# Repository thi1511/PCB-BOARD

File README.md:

# STM32WB55 RF Development Board

## 📌 Giới thiệu

Đây là thiết kế một board phát triển sử dụng vi điều khiển **STM32WB55CEU6**, được thiết kế và layout bằng **KiCad**.

Board tích hợp các khối nguồn 3.3V, USB-C, UART, SWD, BOOT/RESET, mạch dao động và khối RF Front-End với đầu nối RF coaxial.

---

## 🧩 Thành phần chính

- **MCU:** STM32WB55CEU6
- **Nguồn vào:** USB-C 5V
- **Nguồn hệ thống:** +3.3V
- **LDO:** MIC5365-3.3YD5
- **USB:** USB Type-C
- **Debug/Programming:** SWD Header
- **UART:** UART Header
- **RF Front-End:** DLF162500LT-502BA1
- **RF Connector:** Coaxial RF Connector
- **High-Speed Crystal:** 32 MHz
- **Low-Speed Crystal:** 32.768 kHz
- **BOOT:** BOOT0 Push Button
- **RESET:** NRST
- **LED:** Status LED

---

## 🔌 Các giao tiếp

### USB-C

USB-C được sử dụng để cấp nguồn và kết nối với board.

### UART

UART Header được sử dụng để giao tiếp UART với vi điều khiển.

### SWD

SWD Header hỗ trợ:

- Nạp firmware
- Debug chương trình
- Kết nối ST-LINK

### RF

Khối RF được kết nối từ STM32WB55CEU6 đến RF Front-End và đầu nối coaxial.

---

## ⚡ Khối nguồn

Nguồn **5V từ USB-C** được đưa qua IC **MIC5365-3.3YD5** để tạo nguồn **+3.3V** cho hệ thống.

Các tụ bypass và decoupling được bố trí xung quanh MCU và các khối nguồn nhằm đảm bảo nguồn hoạt động ổn định.

---

## ⏱️ Clock

Board sử dụng hai nguồn clock:

- **32 MHz crystal:** High-Speed External Clock
- **32.768 kHz crystal:** Low-Speed External Clock

---

## 🎛️ BOOT & RESET

Board được tích hợp:

- **BOOT0 Push Button:** lựa chọn chế độ boot
- **NRST:** reset MCU

---

## 📐 PCB Design

PCB được thiết kế bằng **KiCad**.

### PCB Layout

### PCB 3D View

---

## 🖥️ Schematic

Sơ đồ nguyên lý của board:

---

## 📁 Cấu trúc thư mục

```text
STM32WB55-RF-Board/
│
├── README.md
│
├── Schematic/
│   └── STM32WB55.kicad_sch
│
├── PCB/
│   ├── STM32WB55.kicad_pcb
│   └── Gerber/
│
├── Images/
│   ├── schematic.png
│   ├── pcb_layout.png
│   └── pcb_3d.png
│
├── 3D_Models/
│   └── ...
│
└── Libraries/
    └── ...

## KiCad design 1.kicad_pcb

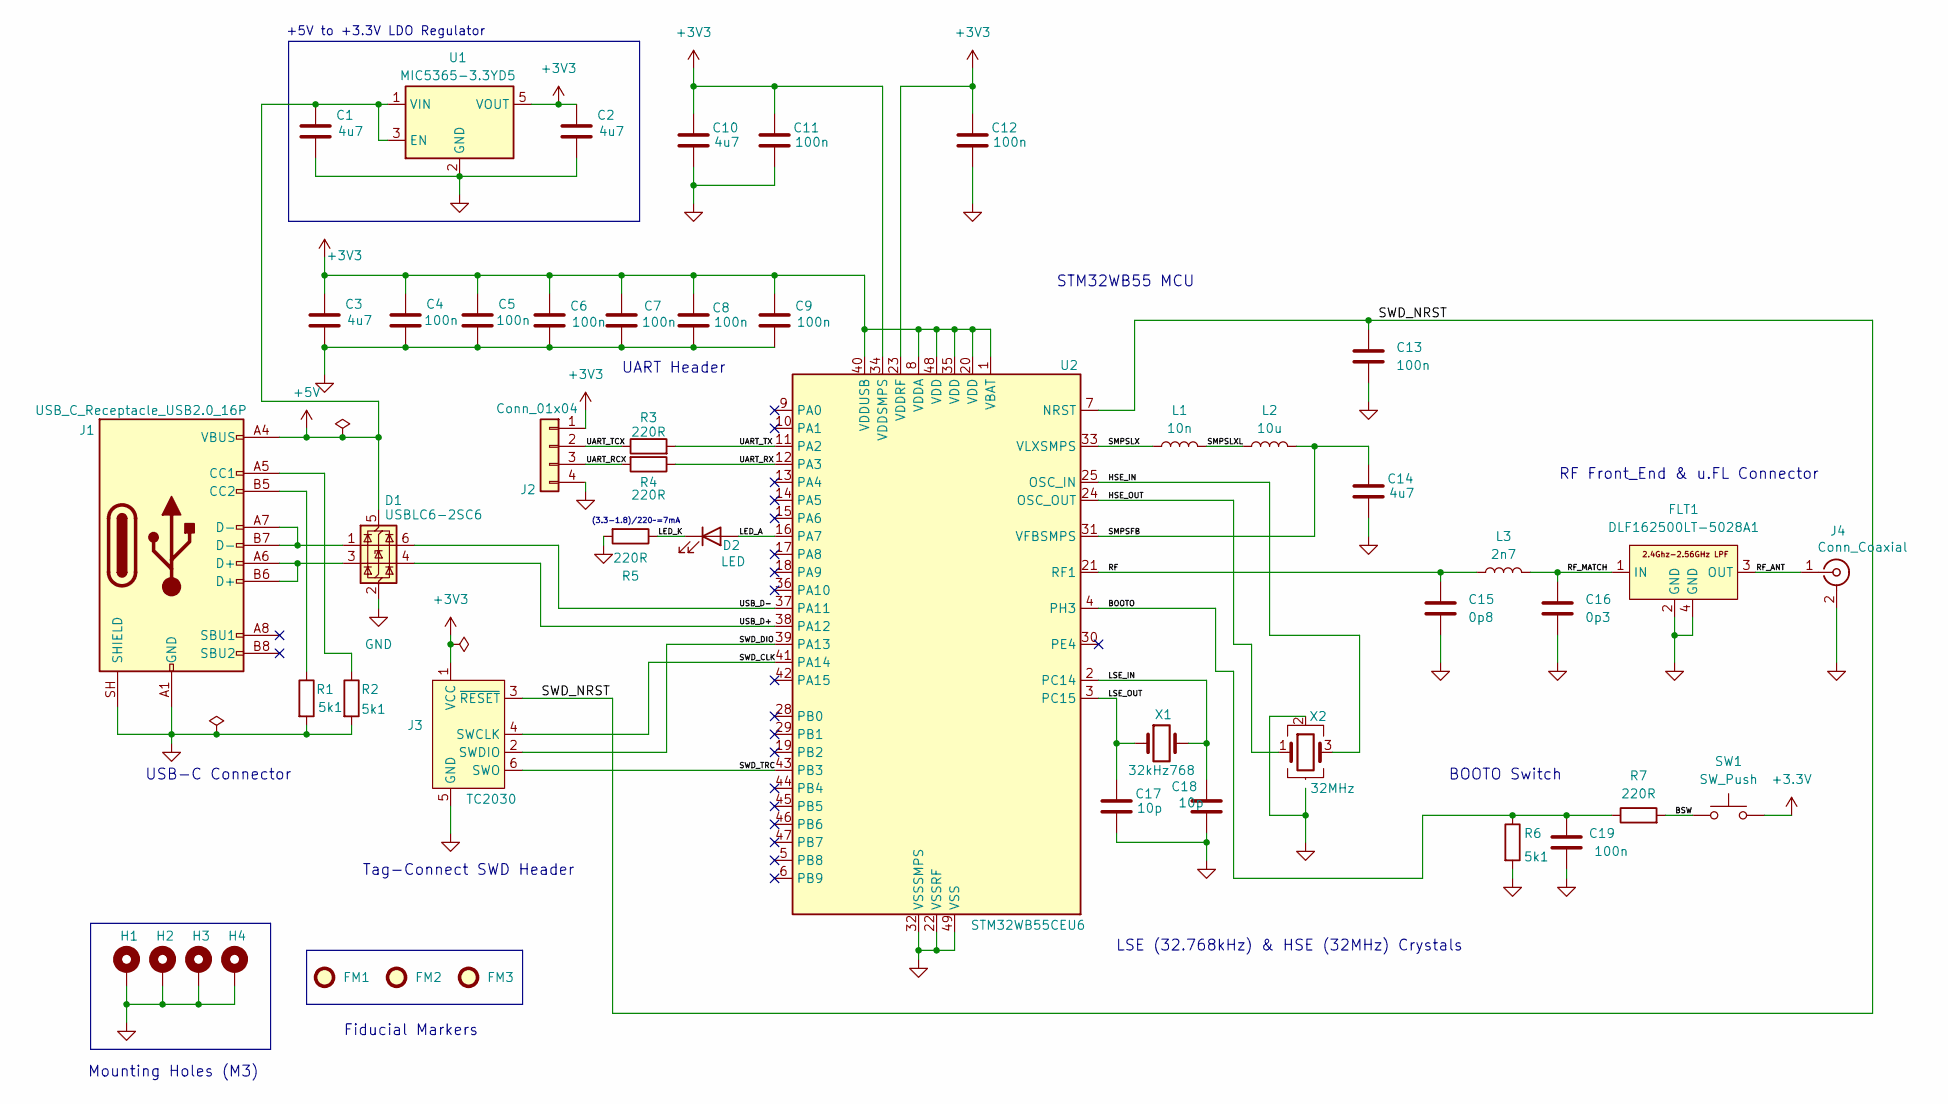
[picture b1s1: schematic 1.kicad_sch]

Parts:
C1, C2, C3, C10, C14: 4u7; C_0603_1608Metric
C4, C5, C6, C7, C8, C9, C11, C12, C13, C19: 100n; C_0402_1005Metric
C15: 0p8; C_0402_1005Metric
C16: 0p3; C_0402_1005Metric
C17, C18: 10p; C_0402_1005Metric_Pad0.74x0.62mm_HandSolder
D1: USBLC6-2SC6; SOT-23-6
D2: LED; LED_0402_1005Metric
FLT1: DLF162500LT-5028A1
FM1, FM2, FM3: Fiducial; Fiducial_1mm_Mask2mm
H1, H2, H3, H4: MountingHole_Pad; MountingHole_2.2mm_M2_Pad_Via
J1: USB_C_Receptacle_USB2.0_16P; USB_C_Receptacle_GCT_USB4105-xx-A_16P_TopMnt_Horizontal
J2: Conn_01x04; Molex_PicoBlade_53048-0410_1x04_P1.25mm_Horizontal
J3: TC2030; Tag-Connect_TC2030-IDC-FP_2x03_P1.27mm_Vertical
J4: Conn_Coaxial; U.FL_Hirose_U.FL-R-SMT-1_Vertical
L1: 10n; L_0402_1005Metric
L2: 10u; L_0805_2012Metric
L3: 2n7; L_0402_1005Metric
R1, R2, R6: 5k1; R_0402_1005Metric
R3, R4, R5, R7: 220R; R_0402_1005Metric
SW1: SW_Push; SW_SPST_CK_RS282G05A3
U1: MIC5365-3.3YD5; TSOT-23-5
U2: STM32WB55CEU6; QFN-48-1EP_7x7mm_P0.5mm_EP5.6x5.6mm
X1: 32kHz768; Crystal_SMD_2012-2Pin_2.0x1.2mm
X2: 32MHz

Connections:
+3.3V: SW1.2
+3V3: C2.1, C3.1, C4.1, C5.1, C6.1, C7.1, C8.1, C9.1, C10.1, C11.1, C12.1, J2.1, J3.1 (VCC), U1.5 (VOUT), U2.1 (VBAT), U2.8 (VDDA), U2.20 (VDD), U2.23 (VDDRF), U2.34 (VDDSMPS), U2.35 (VDD), U2.40 (VDDUSB), U2.48 (VDD)
+5V: C1.1, D1.5 (VBUS), J1.A4 (VBUS), J1.A9 (VBUS), J1.B4 (VBUS), J1.B9 (VBUS), U1.1 (VIN), U1.3 (EN)
/BOOTO: C19.1, R6.1, R7.1, U2.4 (PH3)
/BSW: R7.2, SW1.1
/HSE_IN: U2.25 (OSC_IN), X2.3
/HSE_OUT: U2.24 (OSC_OUT), X2.1
/LED_A: D2.2 (A), U2.16 (PA7)
/LED_K: D2.1 (K), R5.1
/LSE_IN: C18.1, U2.2 (PC14), X1.2
/LSE_OUT: C17.1, U2.3 (PC15), X1.1
/RF: C15.1, L3.1, U2.21 (RF1)
/RF_ANT: FLT1.3 (OUT), J4.1 (In)
/RF_MATCH: C16.1, FLT1.1 (IN), L3.2
/SMPSFB: C14.1, L2.2, U2.31 (VFBSMPS)
/SMPSLX: L1.1, U2.33 (VLXSMPS)
/SMPSLXL: L1.2, L2.1
/SWD_CLK: J3.4 (SWCLK), U2.41 (PA14)
/SWD_DIO: J3.2 (SWDIO), U2.39 (PA13)
/SWD_NRST: C13.1, J3.3 (~RESET), U2.7 (NRST)
/SWD_TRC: J3.6 (SWO), U2.43 (PB3)
/UART_RCX: J2.3, R4.2
/UART_RX: R4.1, U2.12 (PA3)
/UART_TCX: J2.2, R3.1
/UART_TX: R3.2, U2.11 (PA2)
/USB_D+: D1.4 (I/O2), U2.38 (PA12)
/USB_D-: D1.6 (I/O1), U2.37 (PA11)
unnamed: D1.1 (I/O1), J1.A7 (D-), J1.B7 (D-)
unnamed: D1.3 (I/O2), J1.A6 (D+), J1.B6 (D+)
unnamed: J1.A5 (CC1), R2.1
unnamed: J1.B5 (CC2), R1.1

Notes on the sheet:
Mounting Holes (M3)
BOOTO Switch
LSE (32.768kHz) & HSE (32MHz) Crystals
STM32WB55 MCU
RF Front_End & u.FL Connector
Tag-Connect SWD Header
(3.3-1.8)/220~=7mA
USB-C Connector
+5V to +3.3V LDO Regulator
Fiducial Markers
UART Header

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
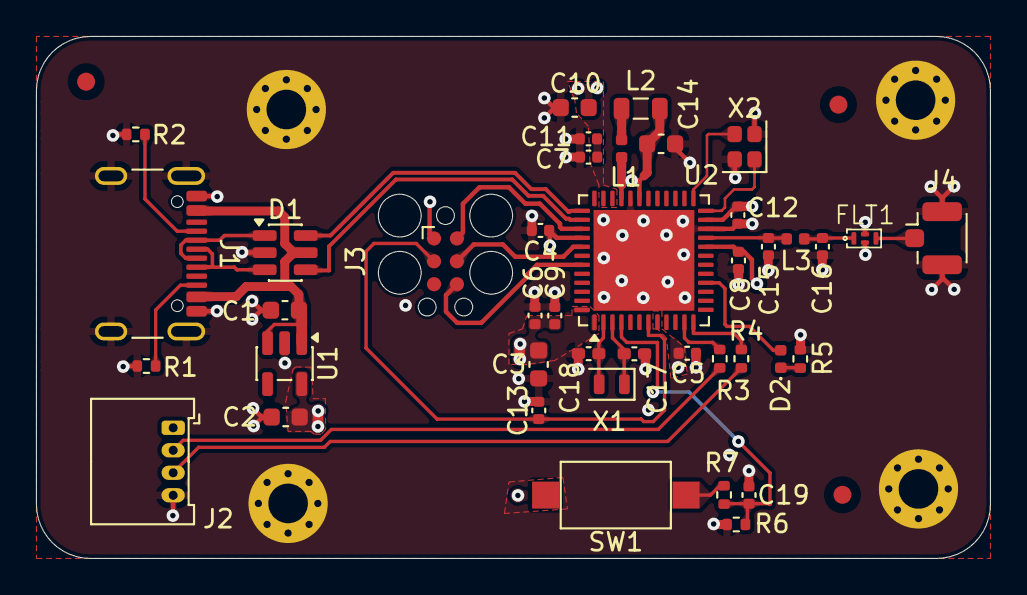
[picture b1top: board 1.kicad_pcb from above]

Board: 4 copper layers, 53.0 x 29.0 mm, 48 parts (0 on the bottom side), 31 nets.
